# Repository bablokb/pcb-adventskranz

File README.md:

Einfache Platine für einen Adventskranz mit vier LEDs
=====================================================

Die Platine ist eine leichte Lötübung mit vier LEDs, vier
Vorwiderständen und einem Button.

Die Steuerung erfolgt über einen Mikrokontroller oder
Raspberry Pi, ein entsprechender Anschluss ist ebenfalls
vorhanden.

Schaltung und Layout
--------------------

Grünzeug aus dem 3D-Drucker
---------------------------

Als "Zubehör" gibt es einen Kranz aus dem 3D-Drucker (Datei
`pcb-adventskranz.stl`).

Quelle: <https://www.tinkercad.com/things/6teYZAPliXV>

(Remix aus:
<https://www.tinkercad.com/things/dioOVePNGom-adventskranz-wreath-terrific-hango-lappi>

Flamme aus dem 3D-Drucker
-------------------------

In transparentem PLA gedruckt, macht sich eine "Flamme" auf der LED
sehr schön (Datei `Flamme_5.1mm.stl`). Das ist eine für 5mm-LEDs passend
skalierte Version von
<https://www.prusaprinters.org/prints/21546-candle-flame-for-vase-mode>.

Lizenz
------

Die Originalmodelle stehen unter der Lizenz ihrer Schöpfer, soweit
angegeben und verfügbar.

Die Lizenz der Platinen und eigenen Entwürfe steht unter der CC-BY-SA
Lizenz.

Shield: [![CC BY-SA 4.0][cc-by-sa-shield]][cc-by-sa]

This work is licensed under a
[Creative Commons Attribution-ShareAlike 4.0 International
License][cc-by-sa].

[![CC BY-SA 4.0][cc-by-sa-image]][cc-by-sa]

[cc-by-sa]: http://creativecommons.org/licenses/by-sa/4.0/
[cc-by-sa-image]: https://licensebuttons.net/l/by-sa/4.0/88x31.png
[cc-by-sa-shield]:
https://img.shields.io/badge/License-CC%20BY--SA%204.0-lightgrey.svg

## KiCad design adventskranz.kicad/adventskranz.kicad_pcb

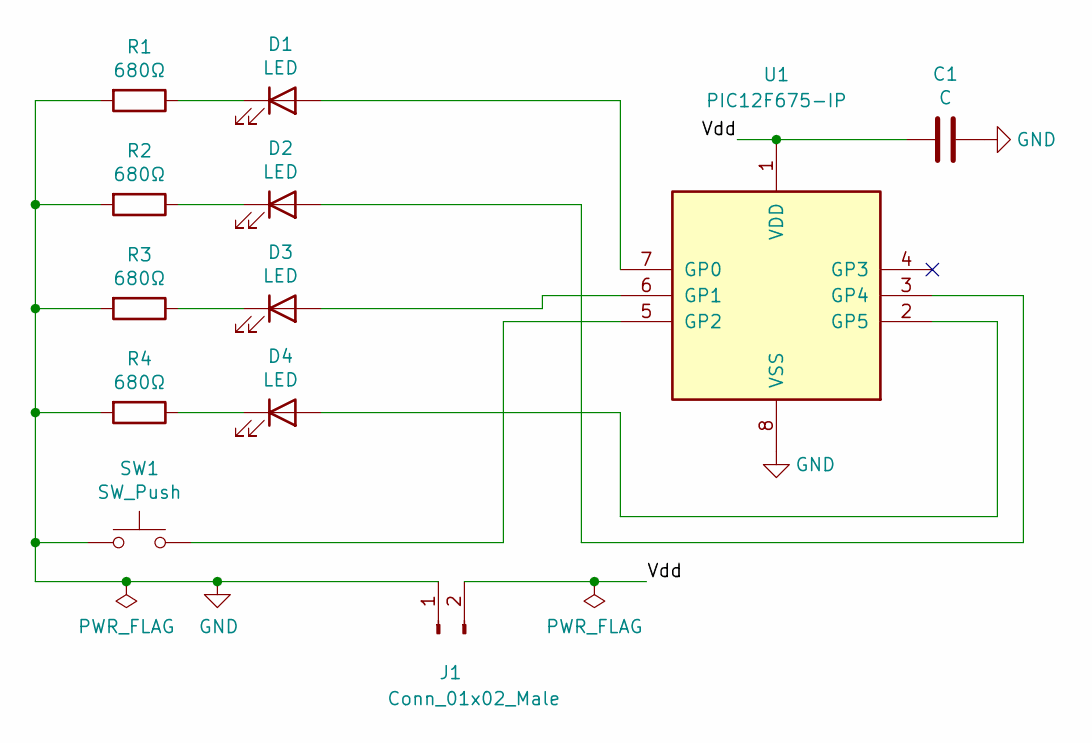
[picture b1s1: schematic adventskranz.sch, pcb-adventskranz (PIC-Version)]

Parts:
C1: C; C_Disc_D3.0mm_W2.0mm_P2.50mm
D1, D2, D3, D4: LED; LED_D5.0mm_Clear
J1: Conn_01x02_Male; PinHeader_1x02_P2.54mm_Vertical
R1, R2, R3, R4: 680Ω; R_Axial_DIN0204_L3.6mm_D1.6mm_P5.08mm_Horizontal
SW1: SW_Push; SW_PUSH_6mm
U1: PIC12F675-IP; DIP-8_W7.62mm

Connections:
/Vdd: C1.2, J1.2, U1.1 (VDD)
GND: C1.1, J1.1, R1.2, R2.2, R3.2, R4.2, SW1.1, U1.8 (VSS)
unnamed: D1.1 (K), R1.1
unnamed: D1.2 (A), U1.7 (GP0)
unnamed: D2.1 (K), R2.1
unnamed: D2.2 (A), U1.3 (GP4)
unnamed: D3.1 (K), R3.1
unnamed: D3.2 (A), U1.6 (GP1)
unnamed: D4.1 (K), R4.1
unnamed: D4.2 (A), U1.2 (GP5)
unnamed: SW1.2, U1.5 (GP2)

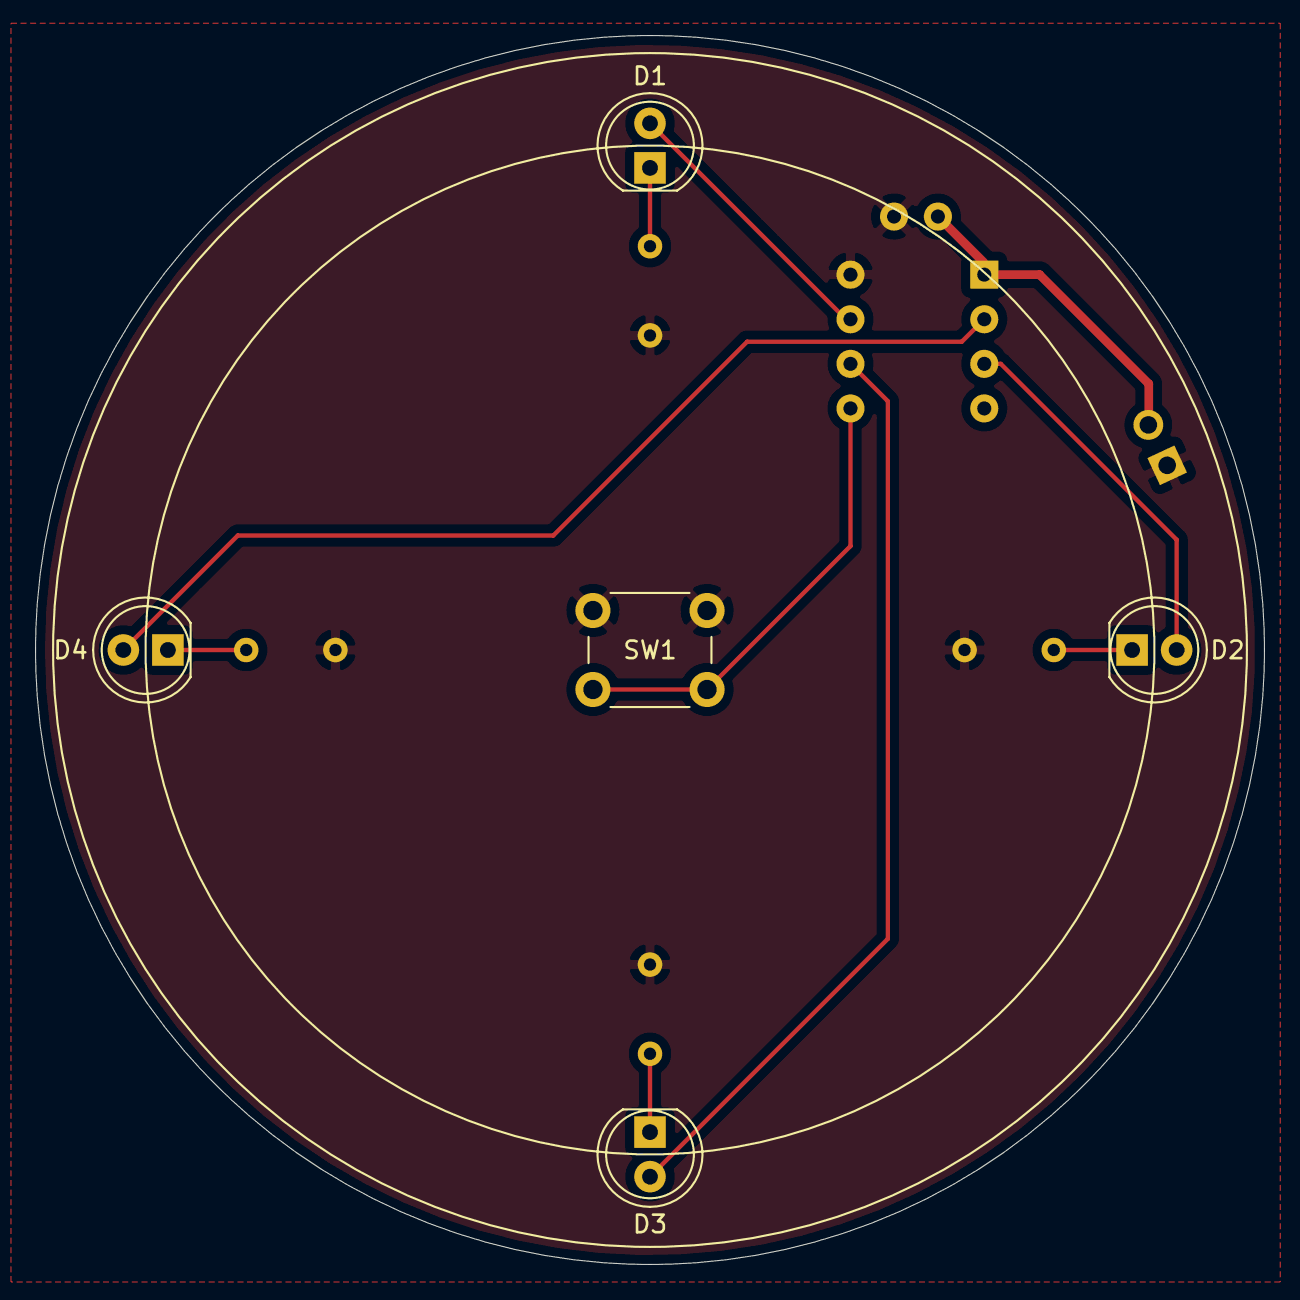
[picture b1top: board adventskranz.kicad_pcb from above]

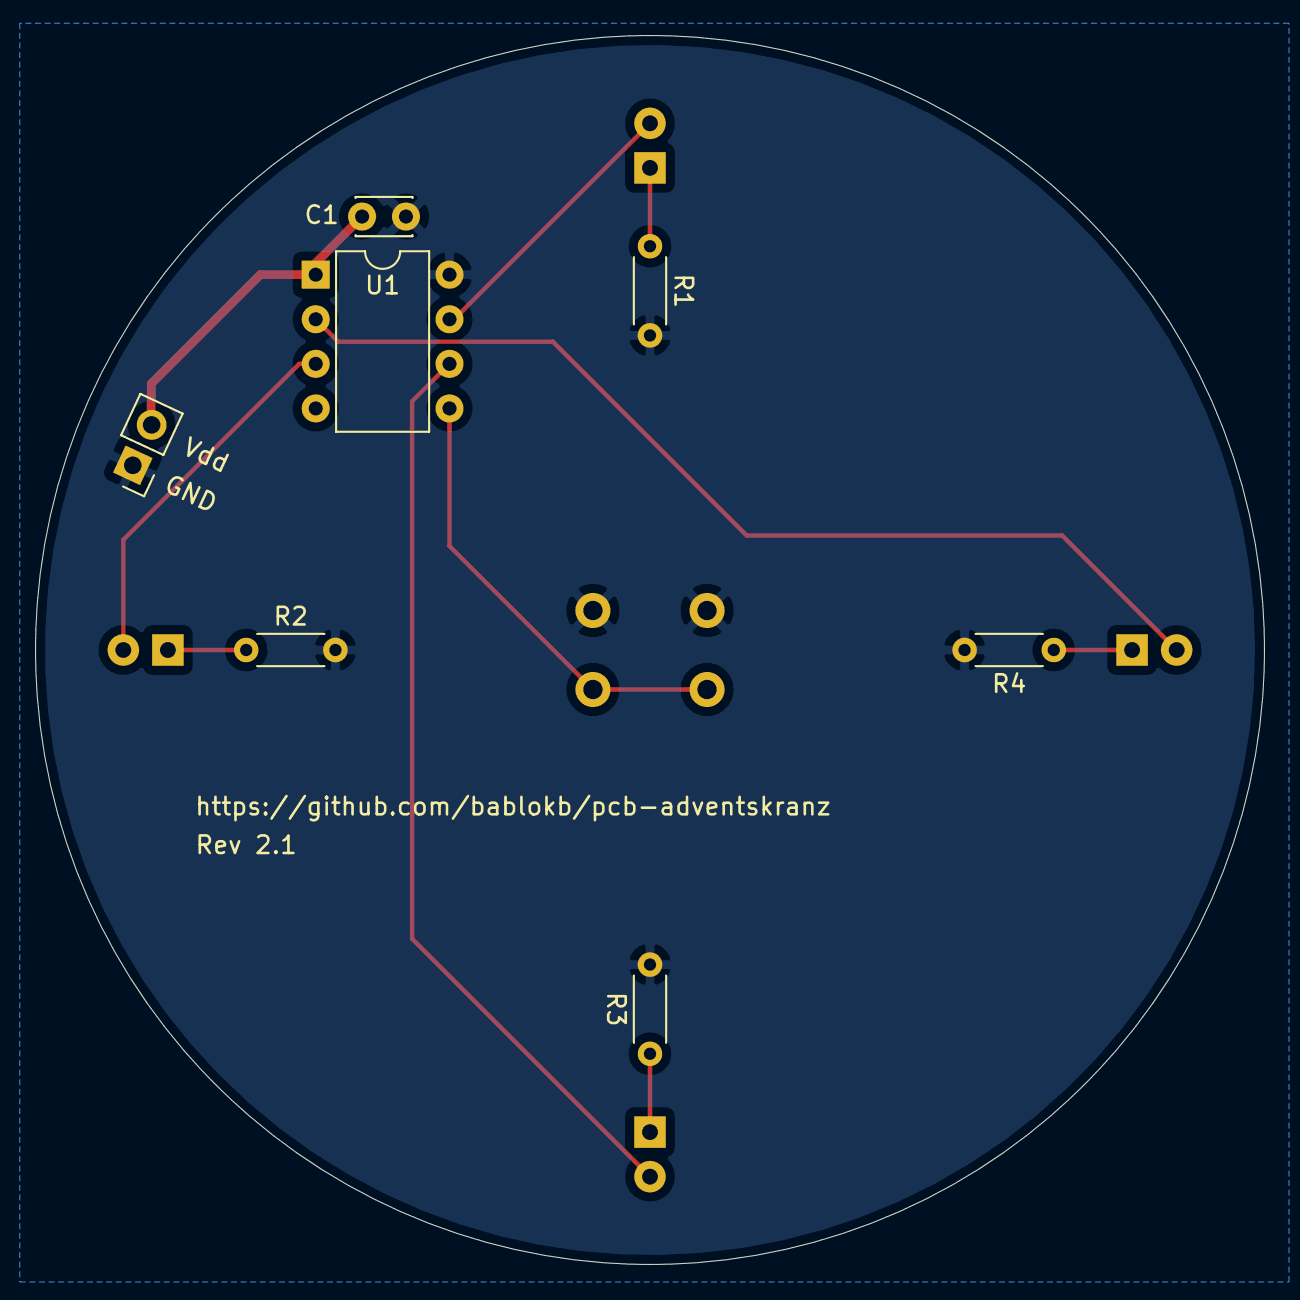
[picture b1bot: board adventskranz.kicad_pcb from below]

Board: 2 copper layers, 70.0 x 70.0 mm, 12 parts (7 on the bottom side), 11 nets.

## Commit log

2021-07-10 changed headline
2021-07-14 update content
2021-07-14 fixed link to image
2021-07-14 Rev 2.1: add PIC for LED-control
2021-07-14 added *.zip
2021-07-15 moved power-connector
2021-07-17 added description of 3D-printed file
2021-07-17 renamed file
2021-07-28 intial commit
2021-07-28 Abschnitt 'Firmware' hinzugefügt
2021-08-07 added info about flame
2021-08-14 set delta to zero
2021-08-19 replaced kranz-3d.png with adventskranz.jpg
2021-10-30 added section about license
